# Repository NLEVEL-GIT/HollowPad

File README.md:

# HollowPad

    HollowPad was my attempt of upgrading my first ever project.. Nanokey. 
    HollowPad features a more flesh out design with 9 keys, a 0.91 inch oled and a rotary encoder.

# Features:

    - 128x32 OLED Display
    - 9 Keys
    - Rotary Encoder

# CAD Model:

    HollowPad is divided in 3 parts.
    - The Main Piece feature holes for M3 brass inserts to screw the PCB in place
    - The Top Piece featuring some designs from Hollow Knight and Silk Song.
    - 2 stand Pieces so that the HackPad can be angled.

    Everything was 100% human made in AutoDesk Fusion. Cuz lowk its free and intuitive!

# PCB
    It was made in KiCad. Only needing a few extra symbols and footprints provided by the Care Package of the HackPad mission from StarDance!

    The footprints for the Switches are standart MX style Switches!

**Schematic:**

**PCB Layout:**

# Firmware Overview
    This hackpad uses [QMK](https://qmk.fm/) firmware for everything. 

    - The 4 keys currently act as macros and are reprogrammable 
    - The OLED just shows some customs drawings i made in Piskel

# BOM:
    Here should be everything you need to make this hackpad

    - 9x Cherry MX Switches
    - 9x DSA Keycaps (or you can 3d print some)
    - 9x 1N4148 DO-35 Diodes.
    - 1x 0.91" 128x32 OLED Display
    - 1x XIAO RP2040
    - 1x Case (5 printed parts or 3 if u dont want the stand)

# Extra stuff
    Honestly this was just a peoject so i could see how far i had come in the little time ive been in stardance and i think it turned out pretty good!
    With all of that said i still suck at code so except some bugs especially on the rotary enconder since that was a pain to figure out.

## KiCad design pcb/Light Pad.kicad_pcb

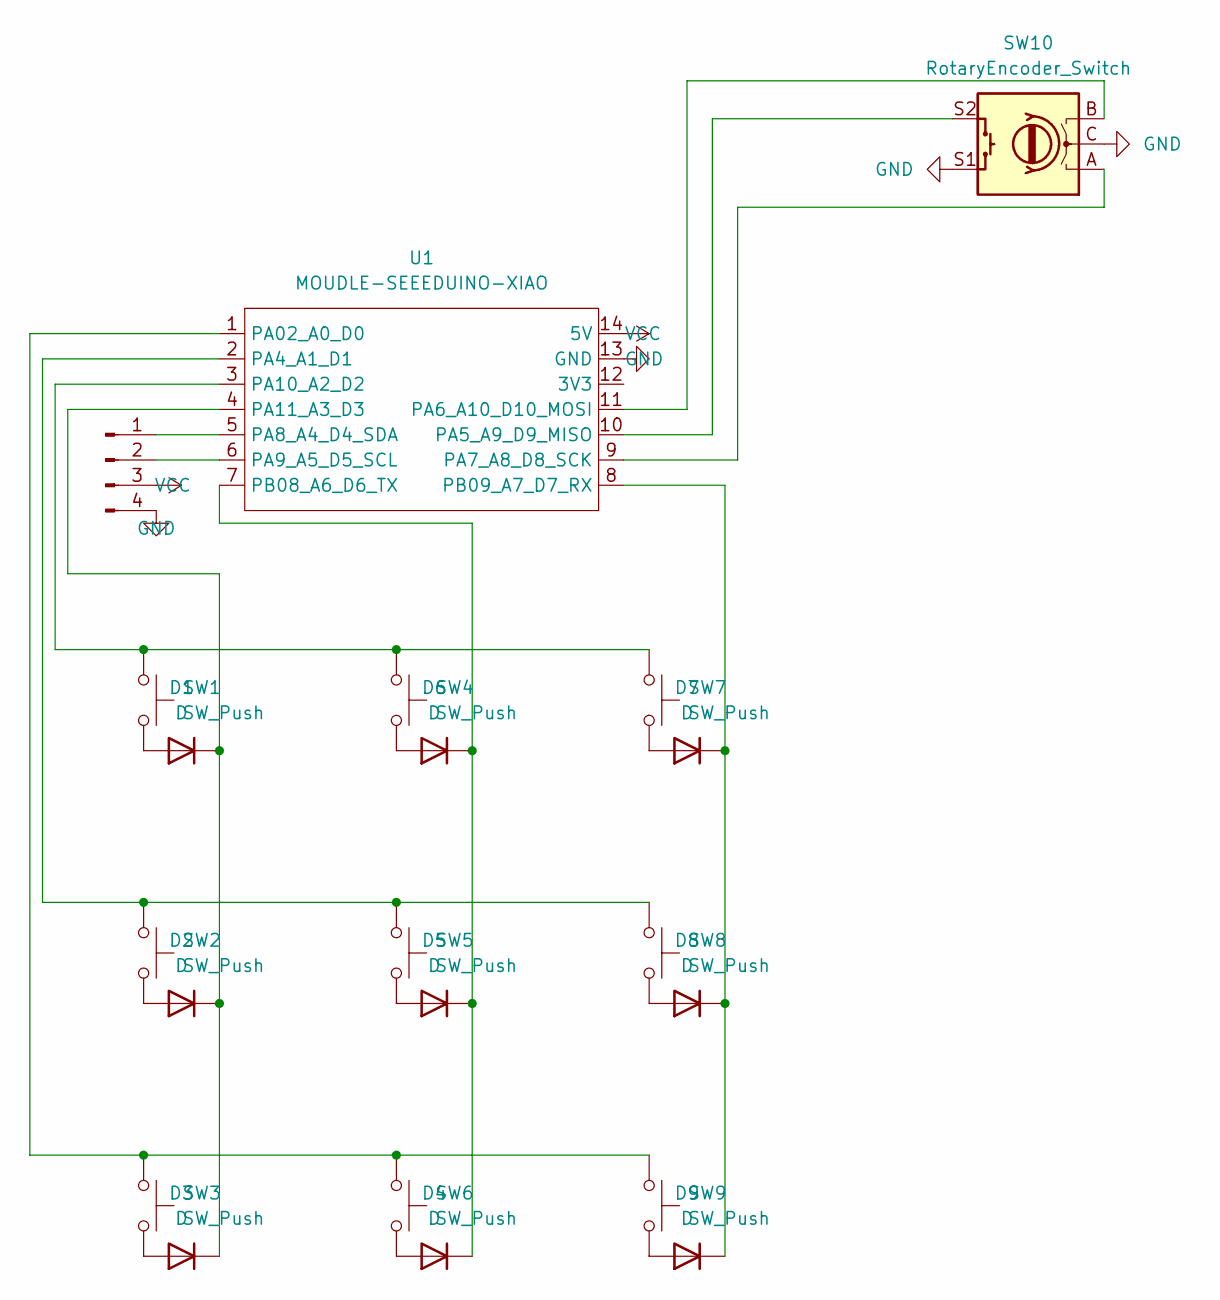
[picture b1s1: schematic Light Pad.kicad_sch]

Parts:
D1, D2, D3, D4, D5, D6, D7, D8, D9: D; D_DO-35_SOD27_P7.62mm_Horizontal
SDA1: Conn_01x04_Pin; PinSocket_1x04_P2.54mm_Vertical
SW1, SW2, SW3, SW4, SW5, SW6, SW7, SW8, SW9: SW_Push; SW_Cherry_MX_1.00u_PCB
SW10: RotaryEncoder_Switch; RotaryEncoder_Alps_EC11E-Switch_Vertical_H20mm
U1: MOUDLE-SEEEDUINO-XIAO; XIAO-RP2040-DIP

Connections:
GND: SDA1.4, SW10.C, SW10.S1, U1.13 (GND); also elsewhere on the board
unnamed: D1.2 (A), SW1.2
unnamed: D1.1 (K), D2.1 (K), D3.1 (K), U1.4 (PA11_A3_D3)
unnamed: D2.2 (A), SW2.2
unnamed: D3.2 (A), SW3.2
unnamed: D4.2 (A), SW6.2
unnamed: D4.1 (K), D5.1 (K), D6.1 (K), U1.7 (PB08_A6_D6_TX)
unnamed: D5.2 (A), SW5.2
unnamed: D6.2 (A), SW4.2
unnamed: D7.2 (A), SW7.2
unnamed: D7.1 (K), D8.1 (K), D9.1 (K), U1.8 (PB09_A7_D7_RX)
unnamed: D8.2 (A), SW8.2
unnamed: D9.2 (A), SW9.2
unnamed 13: SDA1.1, U1.5 (PA8_A4_D4_SDA); also elsewhere on the board
unnamed 14: SDA1.2, U1.6 (PA9_A5_D5_SCL); also elsewhere on the board
unnamed: SW3.1, SW6.1, SW9.1, U1.1 (PA02_A0_D0)
unnamed: SW2.1, SW5.1, SW8.1, U1.2 (PA4_A1_D1)
unnamed 17: SW10.S2, U1.10 (PA5_A9_D9_MISO); also elsewhere on the board
unnamed 18: SW10.B, U1.11 (PA6_A10_D10_MOSI); also elsewhere on the board
unnamed 19: SW10.A, U1.9 (PA7_A8_D8_SCK); also elsewhere on the board
unnamed: SW1.1, SW4.1, SW7.1, U1.3 (PA10_A2_D2)
VCC: SDA1.3, U1.14 (5V); also elsewhere on the board

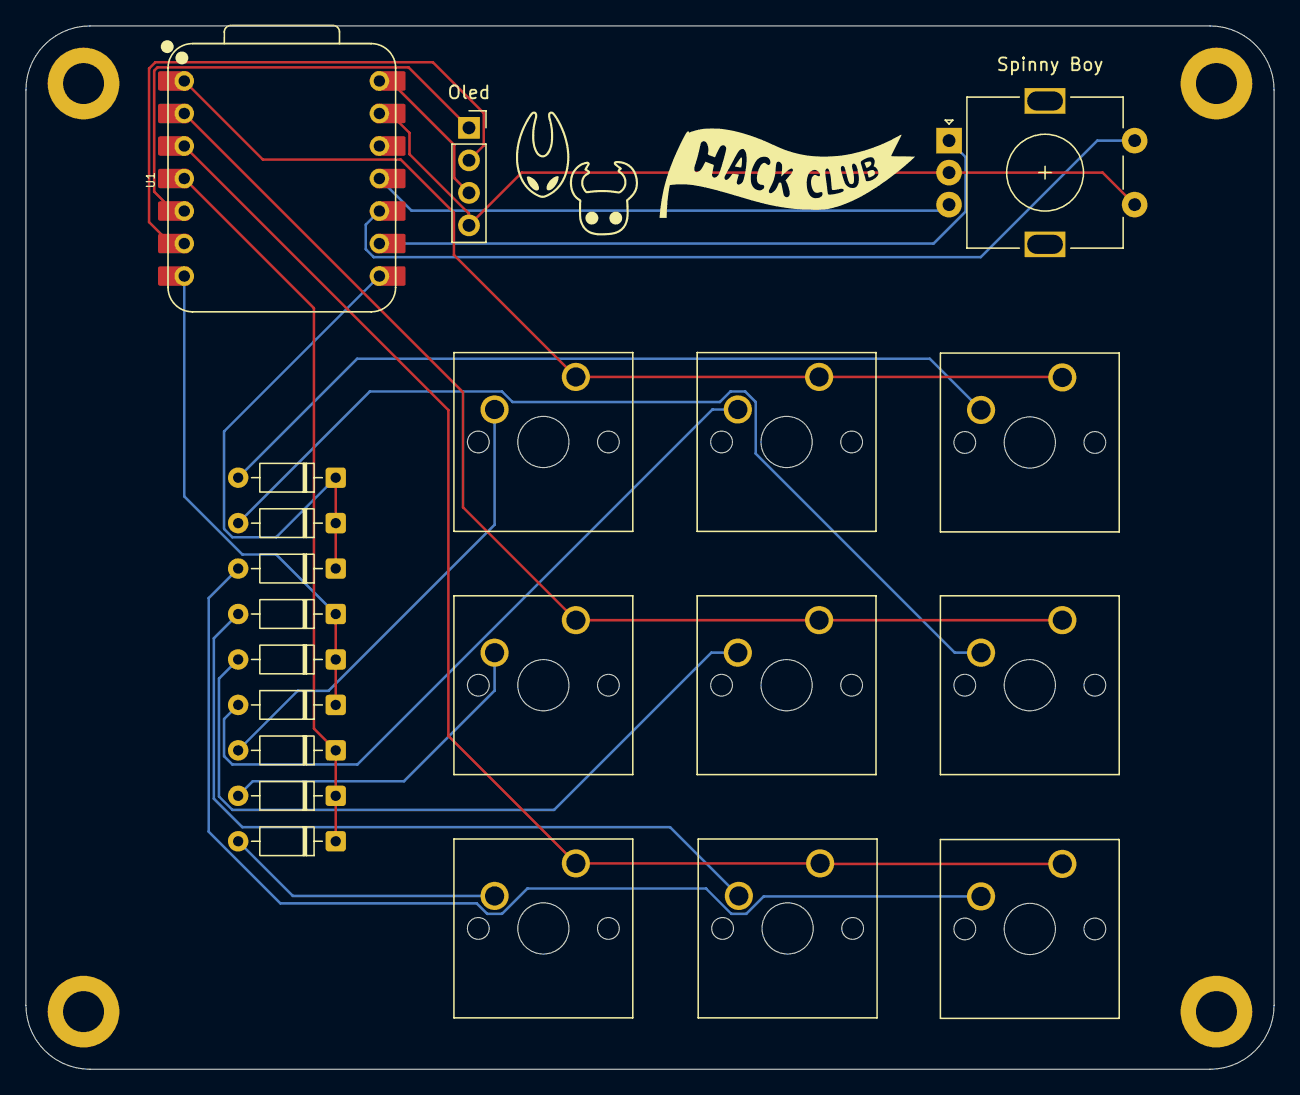
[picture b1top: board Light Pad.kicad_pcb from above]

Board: 2 copper layers, 97.5 x 81.5 mm, 21 parts (0 on the bottom side), 22 nets.

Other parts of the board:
Oled: Conn_01x04_Pin; PinSocket_1x04_P2.54mm_Vertical
Spinny Boy: RotaryEncoder_Switch; RotaryEncoder_Alps_EC11E-Switch_Vertical_H20mm

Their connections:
GND: Oled.4, Spinny Boy.C, Spinny Boy.S1; also elsewhere on the board
unnamed 13: Oled.1; also elsewhere on the board
unnamed 14: Oled.2; also elsewhere on the board
unnamed 17: Spinny Boy.S2; also elsewhere on the board
unnamed 18: Spinny Boy.B; also elsewhere on the board
unnamed 19: Spinny Boy.A; also elsewhere on the board
VCC: Oled.3; also elsewhere on the board
